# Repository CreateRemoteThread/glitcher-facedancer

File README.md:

# glitcher-facedancer

This is a MAX3421 USB addon for [glitcher](https://github.com/createremotethread/glitcher). This is similar in functionality to [facewhisperer](https://github.com/scanlime/facewhisperer) and [facedancer](https://github.com/greatscottgadgets/Facedancer).

The critical improvement is the ability to power cycle the target (MAX4793EUK, 300mA limit) and an on-board microcontroller for experiment automation.

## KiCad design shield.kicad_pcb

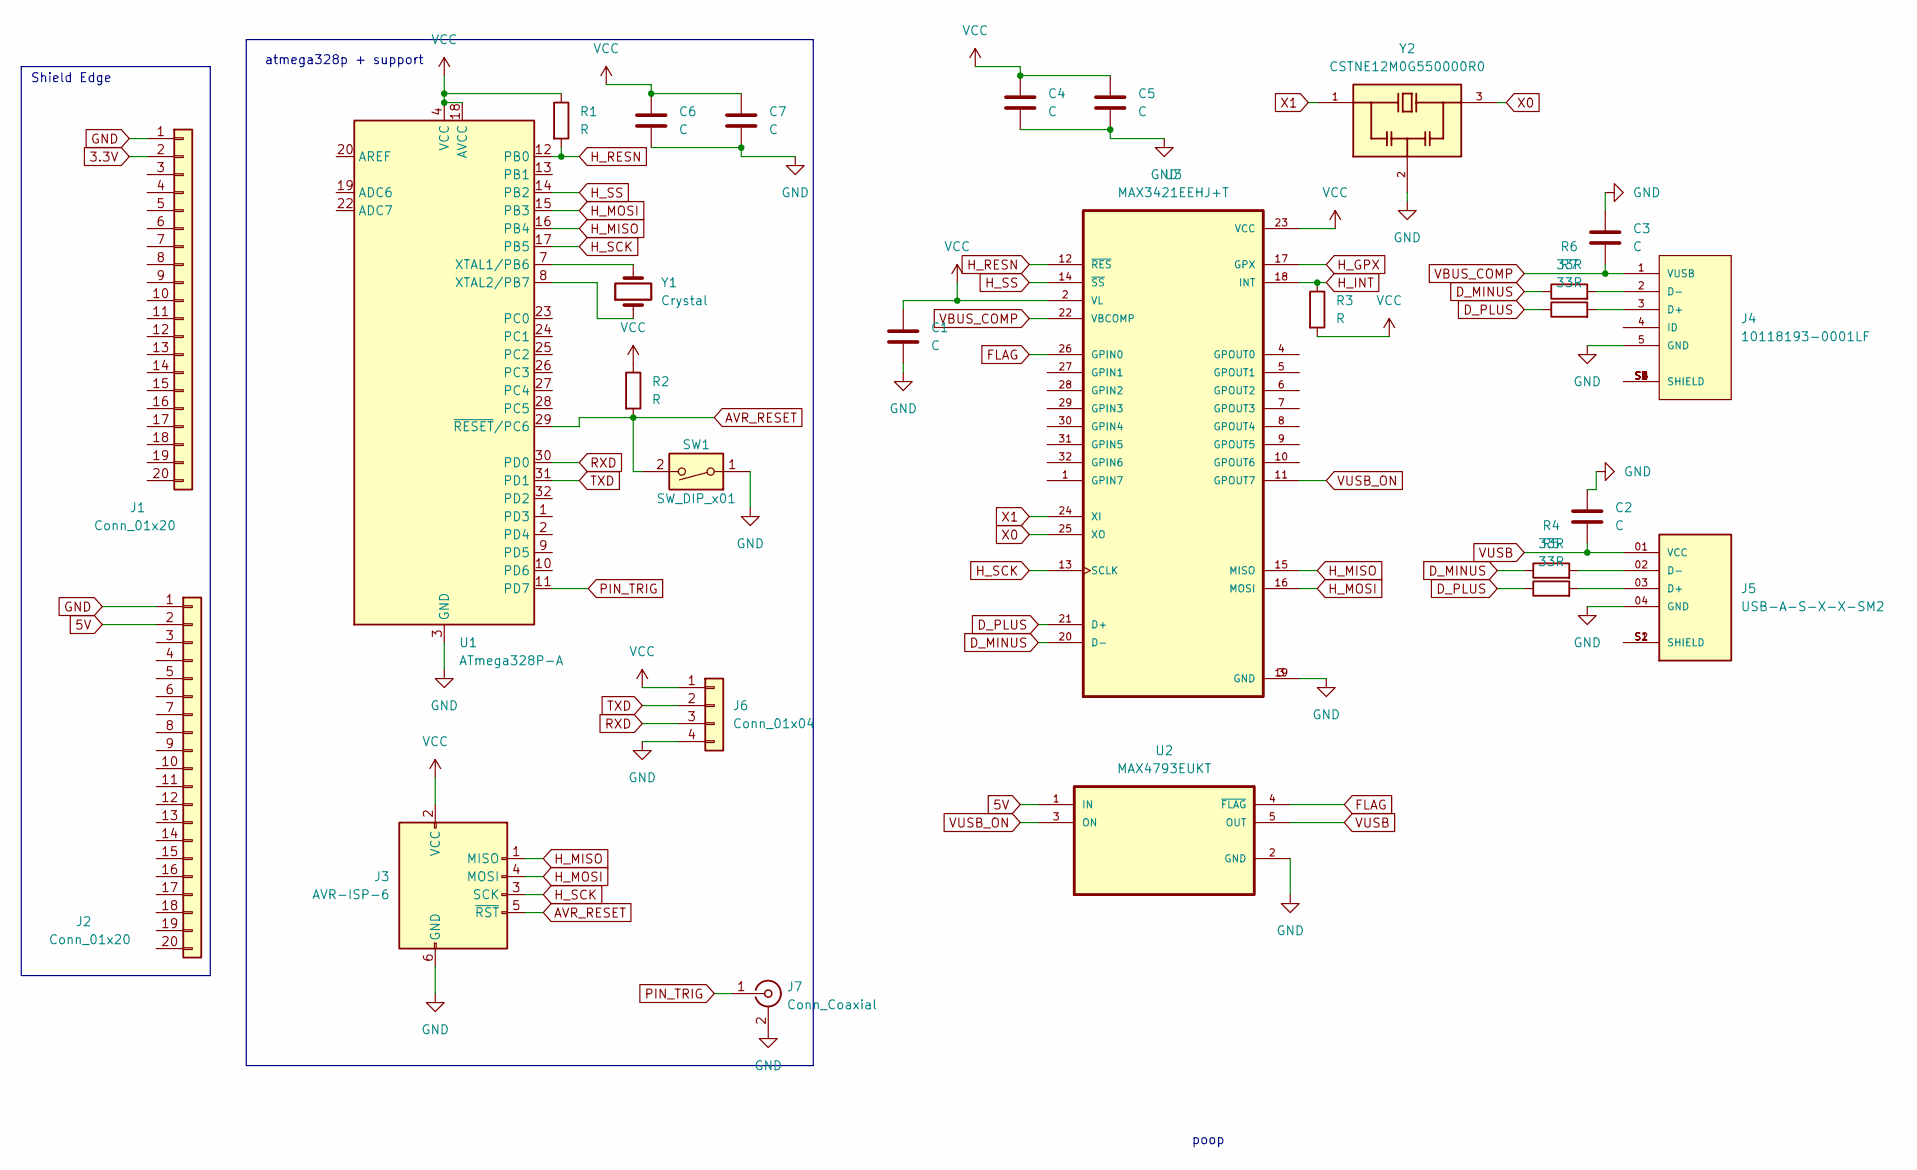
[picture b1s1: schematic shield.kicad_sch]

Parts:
C1, C2, C3, C4, C5, C6, C7: C; C_0603_1608Metric_Pad1.08x0.95mm_HandSolder
J1, J2: Conn_01x20; PinHeader_1x20_P2.54mm_Vertical
J3: AVR-ISP-6; PinHeader_2x03_P2.54mm_Vertical
J4: 10118193-0001LF; FCI_10118193-0001LF
J5: USB-A-S-X-X-SM2; SAMTEC_USB-A-S-X-X-SM2; PARTREV T
J6: Conn_01x04; PinHeader_1x04_P2.54mm_Vertical
J7: Conn_Coaxial; RF2-04A-T-00-50-G
R1, R2, R3: R; R_0603_1608Metric_Pad0.98x0.95mm_HandSolder
R4, R5, R6, R7: 33R; R_0603_1608Metric_Pad0.98x0.95mm_HandSolder
SW1: SW_DIP_x01; PinHeader_Switch
U1: ATmega328P-A; TQFP-32_7x7mm_P0.8mm
U2: MAX4793EUKT; SOT95P280X145-5N
U3: MAX3421EEHJ+T; QFP50P700X700X120-32N
Y1: Crystal; Crystal_HC49-U_Vertical
Y2: CSTNE12M0G550000R0; OSC_CSTNE12M0G550000R0; PARTREV JGC42-8858A

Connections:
3.3V: J1.2
5V: J2.2, U2.1 (IN)
AVR_RESET: J3.5 (~RST), R2.2, SW1.2, U1.29 (~RESET/PC6)
D_MINUS: R4.1, R6.1, U3.20 (D-)
D_PLUS: R5.1, R7.1, U3.21 (D+)
FLAG: U2.4 (~FLAG), U3.26 (GPIN0)
GND: C1.2, C2.1, C3.1, C4.2, C5.2, C6.2, C7.2, J1.1, J2.1, J3.6 (GND), J4.5 (GND), J5.04 (GND), J6.4, J7.2 (Ext), SW1.1, U1.3 (GND), U1.5 (GND), U1.21 (GND), U2.2 (GND), U3.3 (GND), U3.19 (GND), Y2.2
H_GPX: U3.17 (GPX)
H_INT: R3.1, U3.18 (INT)
H_MISO: J3.1 (MISO), U1.16 (PB4), U3.15 (MISO)
H_MOSI: J3.4 (MOSI), U1.15 (PB3), U3.16 (MOSI)
H_RESN: R1.2, U1.12 (PB0), U3.12 (~RES)
H_SCK: J3.3 (SCK), U1.17 (PB5), U3.13 (SCLK)
H_SS: U1.14 (PB2), U3.14 (~SS)
unnamed: J4.2 (D-), R6.2
unnamed: J4.3 (D+), R7.2
unnamed: J4.S1 (SHIELD), J4.S2 (SHIELD), J4.S3 (SHIELD), J4.S4 (SHIELD), J4.S5 (SHIELD), J4.S6 (SHIELD)
unnamed: J5.02 (D-), R4.2
unnamed: J5.03 (D+), R5.2
unnamed: J5.S1 (SHIELD), J5.S2 (SHIELD)
unnamed: U1.7 (XTAL1/PB6), Y1.2
unnamed: U1.8 (XTAL2/PB7), Y1.1
PIN_TRIG: J7.1 (In), U1.11 (PD7)
RXD: J6.3, U1.30 (PD0)
TXD: J6.2, U1.31 (PD1)
VBUS_COMP: C3.2, J4.1 (VUSB), U3.22 (VBCOMP)
VCC: C1.1, C4.1, C5.1, C6.1, C7.1, J3.2 (VCC), J6.1, R1.1, R2.1, R3.2, U1.4 (VCC), U1.6 (VCC), U1.18 (AVCC), U3.2 (VL), U3.23 (VCC)
VUSB: C2.2, J5.01 (VCC), U2.5 (OUT)
VUSB_ON: U2.3 (ON), U3.11 (GPOUT7)
X0: U3.25 (XO), Y2.3
X1: U3.24 (XI), Y2.1

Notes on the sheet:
atmega328p + support
Shield Edge
poop

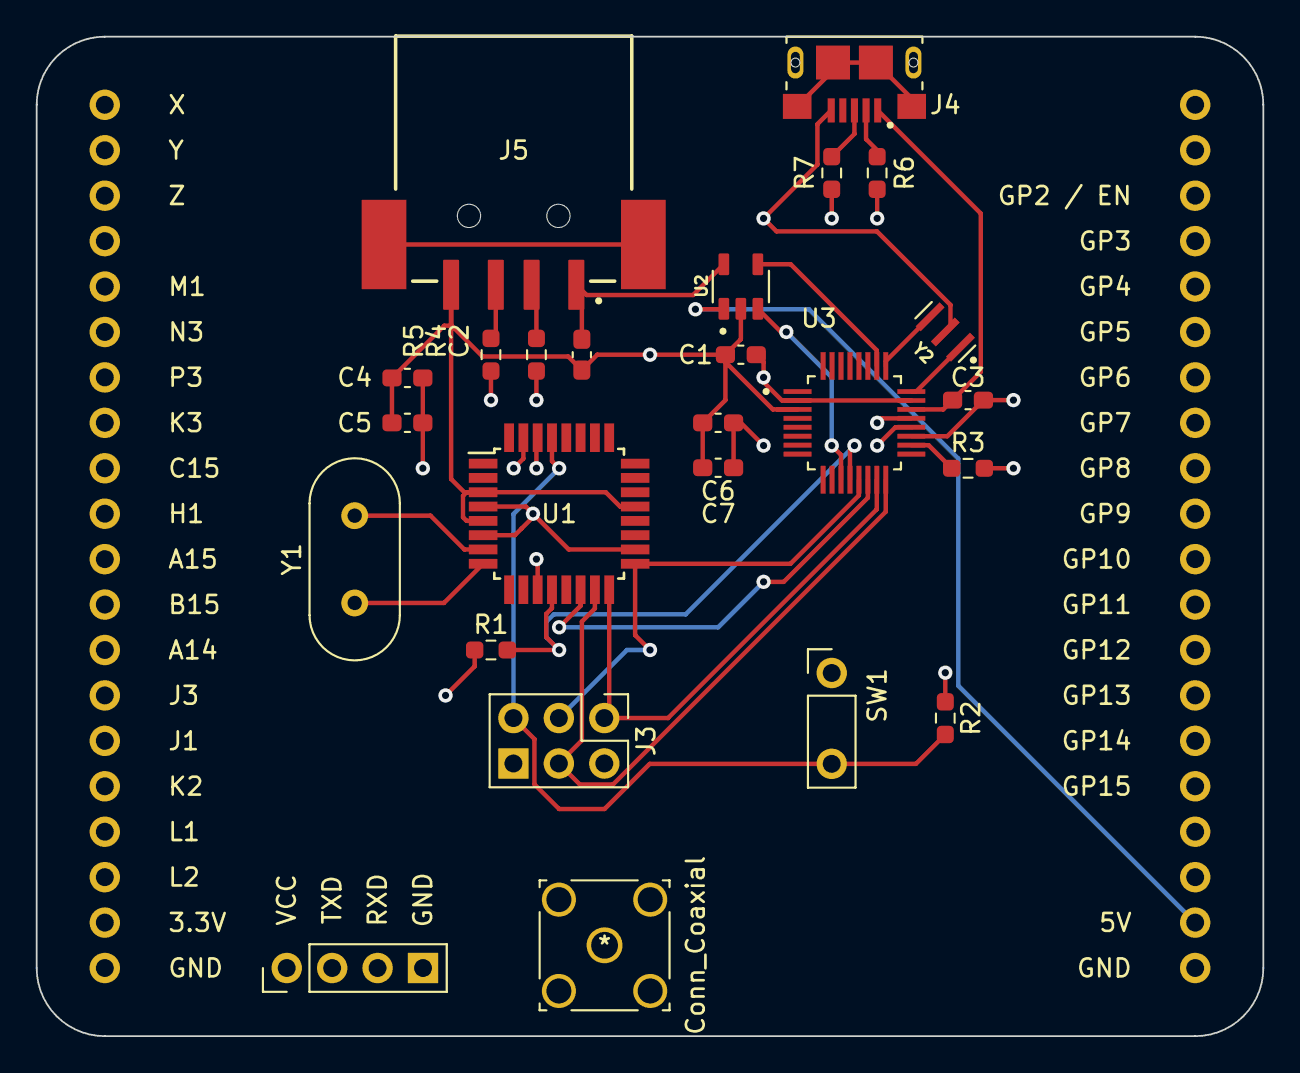
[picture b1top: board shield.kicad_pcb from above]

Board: 4 copper layers, 68.6 x 55.9 mm, 27 parts (0 on the bottom side), 29 nets.

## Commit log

2022-09-12 initial rsrc commit
2022-09-12 poop
2022-09-12 pewpewpew
2022-09-12 save
2022-09-14 decoupling
2022-09-14 dont let your dreams be memes

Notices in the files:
parts and their libraries:
Copyright 2021 Accelerated Designs. All rights reserved.
